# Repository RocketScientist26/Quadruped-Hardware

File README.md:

# Quadruped-Hardware

Main, Battery protection and Servo PCBs for Quadruped robot

Project page: [https://rocket-scientist.me/quadruped.html](https://rocket-scientist.me/quadruped.html)

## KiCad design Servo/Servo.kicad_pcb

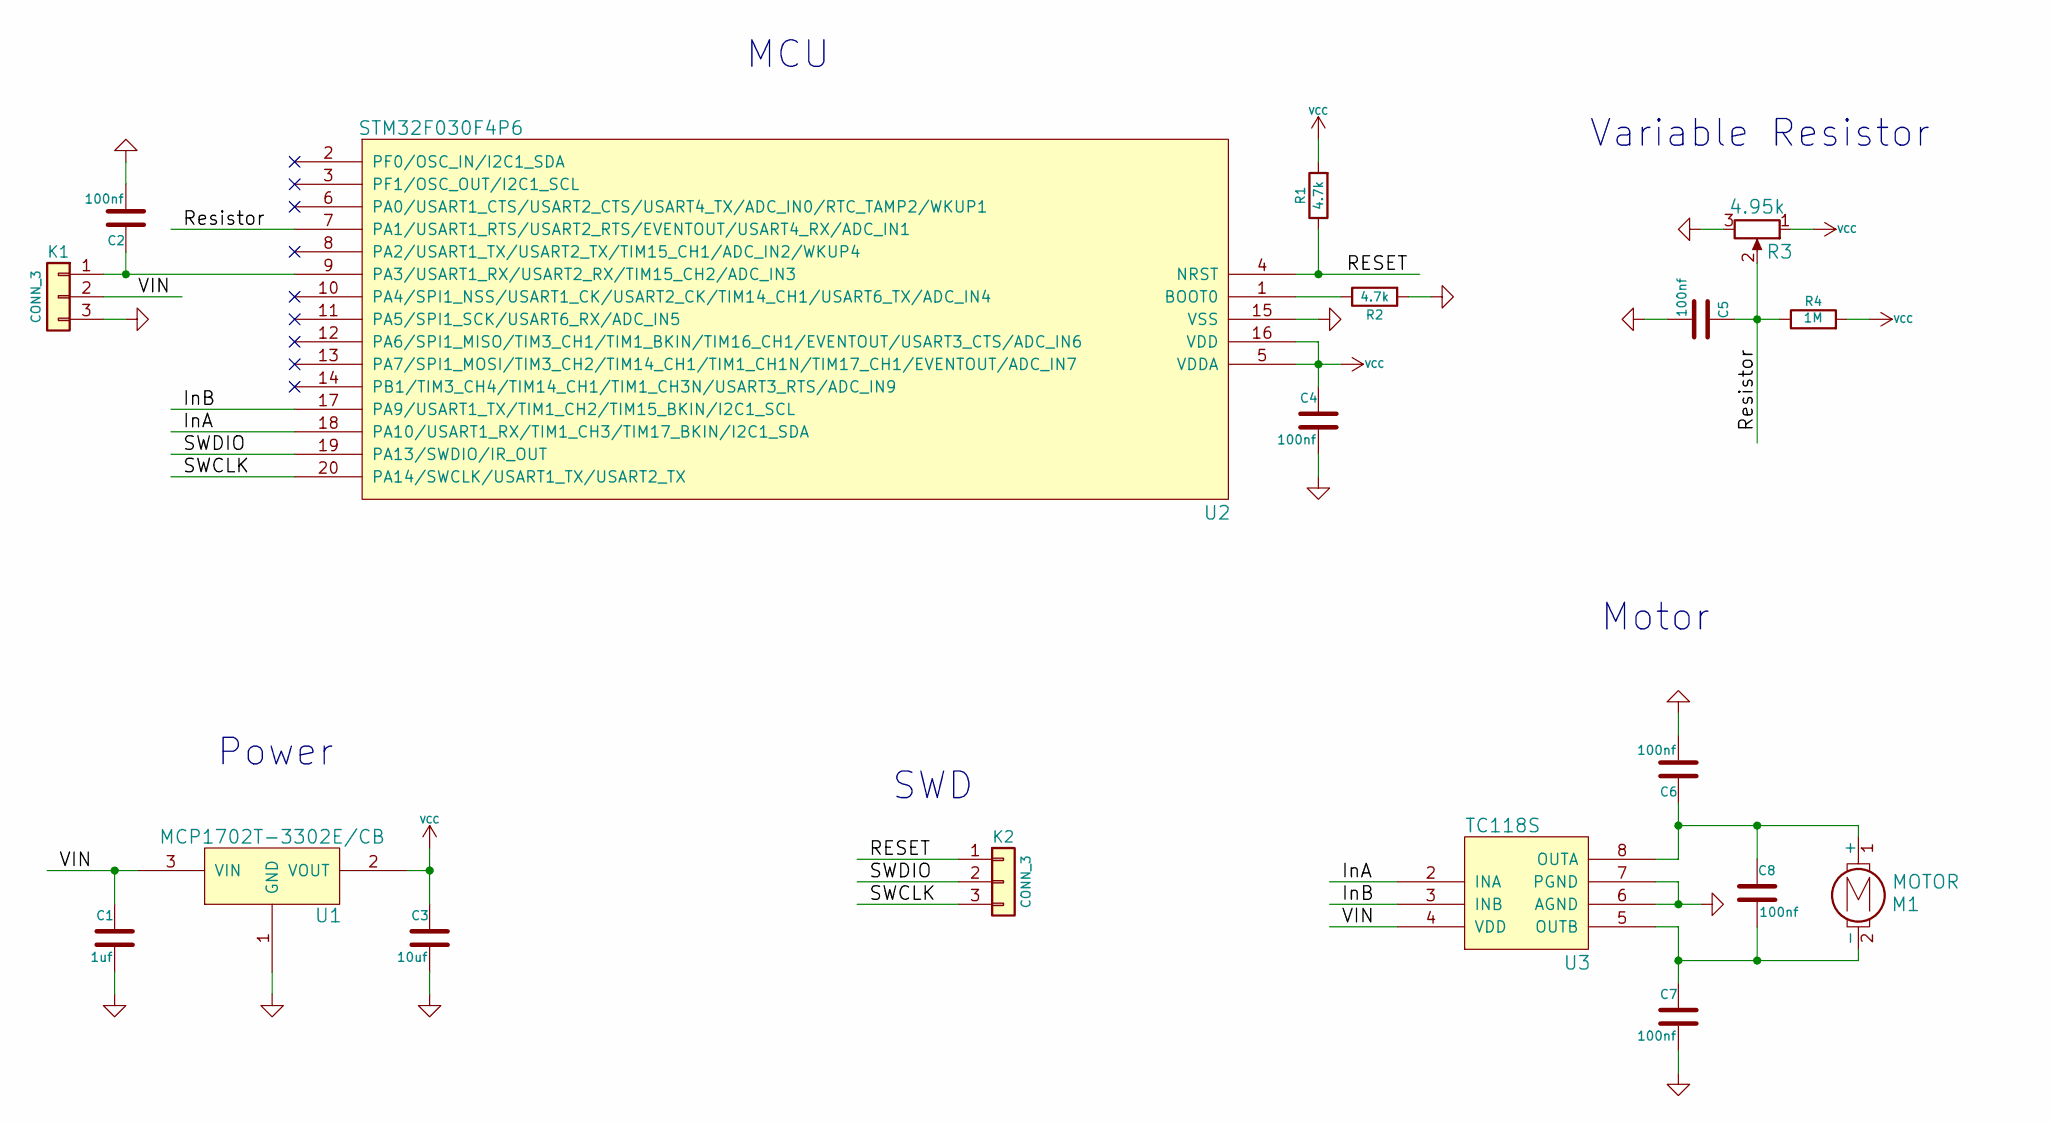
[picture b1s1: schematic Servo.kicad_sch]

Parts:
C1: 1uf; SM0402
C2, C4, C5, C6, C7, C8: 100nf; SM0402
C3: 10uf; SM0402
K1: CONN_3; SIL3_MDS
K2: CONN_3; SIL3_D
M1: MOTOR; SIL2_MD
R1, R2: 4.7k; SM0402
R3: 4.95k; SIL3_MD
R4: 1M; SM0402
U1: MCP1702T-3302E/CB; SOT23
U2: STM32F030F4P6; TSSOP20
U3: TC118S; SOP8

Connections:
/InA: U2.18 (PA10/USART1_RX/TIM1_CH3/TIM17_BKIN/I2C1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), U3.2 (INA)
/InB: U2.17 (PA9/USART1_TX/TIM1_CH2/TIM15_BKIN/I2C1_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), U3.3 (INB)
/RESET: K2.1, R1.1, U2.4 (NRST)
/Resistor: C5.1, R3.2, R4.1, U2.7 (PA1/USART1_RTS/USART2_RTS/EVENTOUT/USAR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)
/SWCLK: K2.3, U2.20 (PA14/SWCLK/USART1_TX/USART2_TX)
/SWDIO: K2.2, U2.19 (PA13/SWDIO/IR_OUT)
/VIN: C1.1, K1.2, U1.3 (VIN), U3.4 (VDD)
GND: C1.2, C2.2, C3.2, C4.2, C5.2, C6.2, C7.2, K1.3, R2.2, R3.3, U1.1 (GND), U2.15 (VSS), U3.6 (AGND), U3.7 (PGND)
unnamed: C2.1, K1.1, U2.9 (PA3/USART1_RX/USART2_RX/TIM15_CH2/ADC_I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), U3.1
unnamed: R2.1, U2.1 (BOOT0)
unnamed: C6.1, C8.1, M1.1 (+), U3.8 (OUTA)
unnamed: C7.1, C8.2, M1.2 (-), U3.5 (OUTB)
VCC: C3.1, C4.1, R1.2, R3.1, R4.2, U1.2 (VOUT), U2.5 (VDDA), U2.16 (VDD)

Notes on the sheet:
MCU
SWD
Variable Resistor
Power
Motor

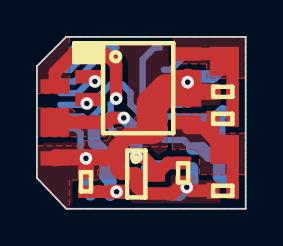
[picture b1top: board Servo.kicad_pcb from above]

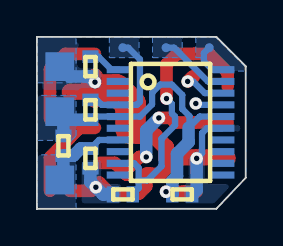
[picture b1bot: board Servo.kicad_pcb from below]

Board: 2 copper layers, 11.6 x 9.5 mm, 18 parts (9 on the bottom side), 13 nets.

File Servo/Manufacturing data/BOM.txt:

-Value-				-Count-		-Package-		-Reference-
1uf					1			0402 SMD		C1
100nf				6			0402 SMD		C2, C4, C5, C6, C7, C8
10uf				1			0402 SMD		C3
4.7k				2			0402 SMD		R1, R2
1M					1			0402 SMD		R4
MCP1702T-3302E/CB	1		 	SOT23			U1
STM32F030F4P6		1		 	TSSOP20			U2
TC118S				1		 	SOP8			U3

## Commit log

2022-04-24 Project files upload
2023-02-23 Update 'README.md'
